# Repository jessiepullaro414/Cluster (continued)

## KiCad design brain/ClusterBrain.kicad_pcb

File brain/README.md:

# brain: the centre-screen board, the same in every car

The Toradex Verdin iMX95 carrier that runs the centre screen, with everything
that does not depend on the car or the panel: the 12 V input and surge
protection (LM74930-Q1), the 5 V buck, the 1.8 V rail, the ignition wake and
sleep control, the private CAN link to the gauges board, the audio codec and
its connectors, two USB-C host ports (J17 on USB_2 and, since 2026-11-06, J19
on USB_1; [docs/audio-and-usb.md](../docs/audio-and-usb.md)), the MFi daughterboard
header, the dial input and the bench headers.

Power (review 2026-11-03, `docs/electrical-review.md` section 9): the
ignition switches the board on through the LM74930's EN pin, and the
module's CTRL_PWR_EN_MOCI holds it on while the module is on or suspended.
So the key starts the module from any state (it boots whenever VCC
appears), and once software powers the module off with the key off, the
board draws only the LM74930's 2.5 uA shutdown current. How long to stay
suspended before powering off is a software setting.

It started as a copy of `display/` (now `archive/display-1966/`, the 1966
Mustang's one-panel carrier). The panel connector, the panel's bias supply,
its polarity jumpers and its backlight driver moved to the panel's own board
(`panel-tsd/`). In their place are two screen ports:

| Port | Ref | Video | Connector |
|---|---|---|---|
| A | J4 | MIPI DSI, 4 lanes + clock | Hirose FH12-40S, 40 contacts |
| B | J18 | LVDS0 + LVDS1 (one single- or dual-link panel) | Hirose FH12-50S, 50 contacts |

Each port has its own current-limited 5 V switch (U6, U7: TPS2557-Q1, 1.61 to
1.98 A), panel reset / enable / backlight-PWM lines held low until software
drives them, an I2C bus, and an analog panel-ID pin. The pin tables and the
rules for a panel board are in [docs/screen-ports.md](../docs/screen-ports.md),
generated from `tools/screen_ports.py`, which this board and every panel board
are built from.

The pairs from the Verdin socket to each port are planned, not autorouted
(`fan_route.py`): straight on F.Cu over the In1 GND plane, 0.16 mm, with GND
guard tracks where the socket has a ground pin between pairs and no length
difference inside a pair. The autorouter is fenced out of both corridors.

The copper that carries the 5 V rail's real current is planned as well
(`power_route.py`): L1 and the output capacitors onto a bar with four vias into
the In3 pour, J1's supply pins onto a bar with two, two at each port switch,
a wide SW_5V, and U2's PGND pins to the input capacitors and their own GND vias.
So does the battery path, J2 to both of the buck's input pins, and each screen
port's 5 V. The rest of +5V carries milliamps and stays autorouted. `route_board.py` runs
`../review/power_sheet.py` on each route, which solves the net with its pours as
copper sheets, and counts a failure as a failed attempt (2026-11-06,
[electrical review](../docs/electrical-review.md) section 9.5b).

Build: `python build_schematic.py`, `python build_pcb.py`, `python route_board.py`,
`python ../run_drc.py ClusterBrain.kicad_pcb`, `python build_bom.py`,
`python ../review/layout_checks.py brain`, `python ../review/review_netlist.py brain`,
`python ../review/usb1_topology.py`. The autorouter varies from run to run, so check
`layout_checks.py` after each route.

127.5 x 95.3 mm since the shrink of 2026-11-06 (section 9.5c of the electrical review). The empty
strips behind J4 and J18 are for the ribbons. `floorplan.py` checks every part against every other,
the corner holes and the module's keep-out.

Not known yet: whether the Verdin iMX95 drives DSI and LVDS as two independent
screens at once (the i.MX 95 itself can; question 9 in `docs/rfq-drafts.md`
section 2), and Hirose's per-contact rating and contact side for the FH12 (the
design assumes 0.5 A).

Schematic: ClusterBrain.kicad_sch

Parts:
C1: 100u 35V hybrid polymer hold-up (Panasonic EEH-ZA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; CP_Elec_8x10
C2: 1u CVS 50V; C_0805_2012Metric
C3: 100n CCAP; C_0603_1608Metric
C4: 100n CTMR; C_0603_1608Metric
C5: 4.7u CIN VIN1; C_1206_3216Metric
C6: 1u VCC; C_0603_1608Metric
C7: 100n boot; C_0603_1608Metric
C8, C54, C59: 22u COUT; C_1206_3216Metric
C9, C64: 10u CIN; C_0805_2012Metric
C10, C65: 10u COUT; C_0805_2012Metric
C11: 100n VCC; C_0603_1608Metric
C12: 100n VIO; C_0603_1608Metric
C13: 4n7 split; C_0603_1608Metric
C39: 100n; C_0603_1608Metric
C40, C44: 100n port switch IN; C_0603_1608Metric
C41, C45: 10u port switch IN; C_0805_2012Metric
C42, C46: 10u port 5V OUT; C_0805_2012Metric
C43, C47: 100n panel-ID filter; C_0603_1608Metric
C53: 10n ignition filter; C_0603_1608Metric
C55: 4.7u CIN VIN2; C_1206_3216Metric
C56: 100n CHF VIN1; C_0603_1608Metric
C57: 100n CHF VIN2; C_0603_1608Metric
C58: 22p CFF; C_0603_1608Metric
C60: 1u dial switch CIN; C_0603_1608Metric
C61: 100n dial signal filter; C_0603_1608Metric
C62: 100n dial click debounce; C_0603_1608Metric
C63: 1u dial 5V filter; C_0603_1608Metric
C66: 10u AVDD; C_0805_2012Metric
C67: 100n AVDD; C_0603_1608Metric
C68: 10u DREG; C_0805_2012Metric
C69: 100n DREG; C_0603_1608Metric
C70: 10u IOVDD; C_0805_2012Metric
C71: 100n IOVDD; C_0603_1608Metric
C72: 1u VREF; C_0603_1608Metric
C73: 1u MICBIAS; C_0603_1608Metric
C74, C75: 1u mic AC couple; C_0603_1608Metric
C76, C77, C78, C79: 4.7u line-out DC block; C_0805_2012Metric
C80, C88: 100n USB switch IN; C_0603_1608Metric
C81, C89: 10u USB switch IN; C_0805_2012Metric
C82, C90: 100u 35V hybrid polymer VBUS (Panasonic EEH-ZA1V1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; CP_Elec_8x10
C83: 1u MFi switch CIN; C_0603_1608Metric
C84: 1u MFi 5V out; C_0603_1608Metric
C85: 10n CdVdT 50V; C_0603_1608Metric
C86: 100n CIN 50V; C_0603_1608Metric
C87: 10n ignition EN filter; C_0603_1608Metric
C91: 100n USB_1_VBUS sense filter; C_0603_1608Metric
D1: SMCJ33CA bidirectional; D_SMC
D5: BAV99-Q ignition clamp (AEC-Q101); SOT-23
D6: BAV99-Q dial signal clamp (AEC-Q101); SOT-23
D7: BAV99-Q dial click clamp (AEC-Q101); SOT-23
D8, D12: SMAJ5.0A VBUS TVS; D_SMA
D9: BAV99-Q LM74930 VS supply diode (AEC-Q101); SOT-23
D10: BAV99-Q ignition EN diode (AEC-Q101); SOT-23
D11: BAV99-Q PWR_EN_MOCI hold diode (AEC-Q101); SOT-23
F1: Keystone 3568 holder, 5A Littelfuse 0297005.WXNV 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; Fuseholder_Blade_Mini_Keystone_3568
J1: Verdin iMX95 Hexa 8GB WB IT; SODIMM-260_DDR4_H4.0-5.2_OrientationStd_Socket
J2: Phoenix MKDS 1,5/3-5,08 power in (DTM06-3S pigtai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; TerminalBlock_Phoenix_MKDS-1,5-3-5.08_1x03_P5.08mm_Horizont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
J3: Molex KK-254 22-27-2031 private CAN link to gauge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; Molex_KK-254_AE-6410-03A_1x03_P2.54mm_Vertical
J4: Screen port A (MIPI DSI), Hirose FH12-40S-0.5SH; Hirose_FH12-40S-0.5SH_1x40-1MP_P0.50mm_Horizontal
J8: Samtec TSW-108-07-G-S JTAG (bench only); PinHeader_1x08_P2.54mm_Vertical
J9: Samtec TSW-104-07-G-S buttons (bench only); PinHeader_1x04_P2.54mm_Vertical
J10: RTC coin cell; BatteryHolder_Keystone_1058_1x2032
J11: Molex KK-254 22-27-2041, rotary dial (PSC-360 + c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; Molex_KK-254_AE-6410-04A_1x04_P2.54mm_Vertical
J12: Samtec TSW-103-07-G-S A55 console UART_3 1.8V (be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; PinHeader_1x03_P2.54mm_Vertical
J13: Samtec TSW-105-07-G-S USB_1 OTG (bench only); PinHeader_1x05_P2.54mm_Vertical
J14: JST XH B5B-XH-A balanced line-out L/R; JST_XH_B5B-XH-A_1x05_P2.50mm_Vertical
J15: JST XH B3B-XH-A electret microphone (2-wire + shi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; JST_XH_B3B-XH-A_1x03_P2.50mm_Vertical
J16: MFi daughterboard header I2C_1, reset, switched 5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; PinHeader_1x06_P2.54mm_Vertical; not fitted
J17, J19: GCT USB4105-GF-A USB-C 2.0 host receptacle; USB_C_Receptacle_GCT_USB4105-xx-A_16P_TopMnt_Horizontal
J18: Screen port B (LVDS), Hirose FH12-50S-0.5SH; Hirose_FH12-50S-0.5SH_1x50-1MP_P0.50mm_Horizontal
L1: 1u XEL5030-102ME 2.1MHz; L_Coilcraft_XAL5030-XXX
L2: 744230900 USB_2 common-mode choke; L_CommonMode_Wurth_WE-CNSW-0603
L3: 744230900 USB_1 common-mode choke; L_CommonMode_Wurth_WE-CNSW-0603
Q1: SQJ460AEP (AEC-Q101, 60V/20V VGS) diode; PowerPAK_SO-8L_Single
Q2: SQJ460AEP (AEC-Q101, 60V/20V VGS) pass; PowerPAK_SO-8L_Single
Q3: PMV55ENEA ignition wake pulldown; SOT-23
R1: 2m 2% sense (Susumu KRL3216E-C-R002-G-T5); R_1206_3216Metric_Kelvin
R2: 49.9R 1% RSET; R_0603_1608Metric
R3: 60.4k RILIM; R_0603_1608Metric
R4: 10k RIMON; R_0603_1608Metric
R5: 100k OV top; R_0603_1608Metric
R6: 2.05k OV bot; R_0603_1608Metric
R7: 100k UV top; R_0603_1608Metric
R8: 11.5k UV bot; R_0603_1608Metric
R9: 0R RBOOT; R_0603_1608Metric
R10: 100k FB top; R_0603_1608Metric
R11: 24.9k FB bot; R_0603_1608Metric
R12: 6.04k RT; R_0603_1608Metric
R13: 100k EN top; R_0603_1608Metric
R14: 24.9k EN bot; R_0603_1608Metric
R15: 100k FLT pu; R_0603_1608Metric
R16: 100k PG pu; R_0603_1608Metric
R17: 124k FB top; R_0603_1608Metric
R18, R60: 100k FB bot; R_0603_1608Metric
R19, R20: 60R term; R_0603_1608Metric
R21: 10k STB pd; R_0603_1608Metric
R37, R77: 61.9k 1% port ILIM (1.6-2.0 A); R_0603_1608Metric
R38, R78: 100k port 5V enable pull-down; R_0603_1608Metric
R39, R70, R79, R92: 100k FAULT pull-up to +1V8; R_0603_1608Metric
R40, R80: 10k 1% panel-ID pull-up to +1V8; R_0603_1608Metric
R41, R81: 100k panel reset pull-down; R_0603_1608Metric
R42, R82: 100k panel enable pull-down; R_0603_1608Metric
R43, R83: 100k backlight PWM pull-down; R_0603_1608Metric
R47: 10k pullup; R_0603_1608Metric
R48: 10k JTAG Vref; R_0603_1608Metric
R49: 47k min; R_0603_1608Metric
R50, R75, R84, R85: 2.2k I2C pull-up to +1V8; R_0603_1608Metric
R51: 56k ignition series; R_0603_1608Metric
R52: 33k ignition divider bottom; R_0603_1608Metric
R53: 10k wake pull-up to +1V8; R_0603_1608Metric
R54: 22.1k dial signal divider top; R_0603_1608Metric
R55: 1k dial signal series; R_0603_1608Metric
R56: 1k dial click series; R_0603_1608Metric
R57: 10k dial click pull-up to +1V8; R_0603_1608Metric
R58: 10.2k dial signal divider bottom; R_0603_1608Metric
R59: 316k 1% FB top; R_0603_1608Metric
R61: 2.2k I2C1 SDA pull-up; R_0603_1608Metric
R62: 2.2k I2C1 SCL pull-up; R_0603_1608Metric
R63: 2.2k mic bias; R_0603_1608Metric
R64: 100R mic return; R_0603_1608Metric
R65, R66, R67, R68: 100R line-out series; R_0603_1608Metric
R69: 61.9k 1% USB ILIM (1.6-2.0 A); R_0603_1608Metric
R71: 22k Rp CC1 (1.5 A, +/-5 percent or better); R_0603_1608Metric
R72: 22k Rp CC2 (1.5 A, +/-5 percent or better); R_0603_1608Metric
R73, R93: 100k USB EN pull-down; R_0603_1608Metric
R74: 100k MFi switch off in reset; R_0603_1608Metric
R76: 10k touch INT pull-up to +1V8; R_0603_1608Metric
R86: 100k SPI CS pull-up to +1V8; R_0603_1608Metric
R87: 100R RG; R_0603_1608Metric
R88: 100k ignition EN top; R_0603_1608Metric
R89: 33k ignition EN bottom; R_0603_1608Metric
R90: 100k EN pull-down; R_0603_1608Metric
R91: 100k 1% USB ILIM (0.95-1.27 A); R_0603_1608Metric
R94: 56k Rp CC1 (default USB current, +/-20 percent or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; R_0603_1608Metric
R95: 56k Rp CC2 (default USB current, +/-20 percent or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; R_0603_1608Metric
R96: 1k USB_1_VBUS sense series; R_0603_1608Metric
U1: LM74930-Q1; Texas_RGE0024H_VQFN-24-1EP_4x4mm_P0.5mm_EP2.7x2.7mm
U2: LM61460-Q1; TI_RJR0014A_VQFN-HR-14_4x3.5mm
U3: TLV767-Q1; Texas_DRB0008A
U4: TCAN1044V-Q1; SOIC-8_3.9x4.9mm_P1.27mm
U6, U7, U11, U16: TPS2557-Q1; Texas_DRB0008A
U8: TPS22918-Q1 (AEC-Q100 G2) dial 5V switch; SOT-23-6
U9: TAC5112-Q1; QFN-32-1EP_5x5mm_P0.5mm_EP3.7x3.7mm_ThermalVias
U10: TLV767-Q1 (3.3 V audio AVDD); Texas_DRB0008A
U12: TPD4E02B04-Q1 line-out ESD (bidirectional, review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; USON-10_2.5x1.0mm_P0.5mm
U13: TPD4E05U06-Q1 mic ESD; USON-10_2.5x1.0mm_P0.5mm
U14, U17: TPD4E05U06-Q1 USB ESD; USON-10_2.5x1.0mm_P0.5mm
U15: TPS22918-Q1 (AEC-Q100 G2) MFi 5V switch; SOT-23-6

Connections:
+1V8: C10.1, C12.1, C70.1, C71.1, D6.2 (K2), D7.2 (K2), J4.7 (+1V8), J16.6 (V1V8), J18.42 (+1V8), R17.1, R39.2, R40.2, R47.2, R48.2, R50.2, R53.1, R57.1, R61.2, R62.2, R70.2, R75.2, R76.2, R79.2, R80.2, R84.2, R85.2, R86.2, R92.2, U3.1 (OUT), U4.5 (VIO), U9.7 (IOVDD)
+3V3: C65.1, C66.1, C67.1, R59.1, U9.31 (AVDD), U10.1 (OUT)
+5V: C8.1, C9.1, C11.1, C40.1, C41.1, C44.1, C45.1, C54.1, C58.1, C59.1, C60.1, C64.1, C80.1, C81.1, C83.1, C88.1, C89.1, D5.2 (K2), J1.251 (VCC), J1.253 (VCC), J1.255 (VCC), J1.257 (VCC), J1.259 (VCC), L1.2, R10.1, R15.2, R16.2, R71.2, R72.2, R94.2, R95.2, U2.1 (BIAS), U3.8 (IN), U4.3 (VCC), U6.2 (IN1), U6.3 (IN2), U7.2 (IN1), U7.3 (IN2), U8.1 (VIN), U10.8 (IN), U11.2 (IN1), U11.3 (IN2), U15.1 (VIN), U16.2 (IN1), U16.3 (IN2)
+12V_PROT: C1.1, C5.1, C55.1, C56.1, C57.1, R1.2, R13.1, U2.8 (VIN1), U2.12 (VIN2)
AOUT_L_N: R66.1, U9.27 (OUT1M)
AOUT_L_N_R: C77.1, R66.2
AOUT_L_P: R65.1, U9.28 (OUT1P)
AOUT_L_P_R: C76.1, R65.2
AOUT_R_N: R68.1, U9.30 (OUT2M)
AOUT_R_N_R: C79.1, R68.2
AOUT_R_P: R67.1, U9.29 (OUT2P)
AOUT_R_P_R: C78.1, R67.2
BOOT_C: C7.1, R9.2, U2.14 (CBOOT)
BOOT_R: R9.1, U2.13 (RBOOT)
BRAIN_EN: D10.3 (CA), D11.3 (CA), R90.1, U1.6 (EN)
CAN1_H: J3.1 (CANH), R19.1, U4.7 (CANH)
CAN1_L: J3.2 (CANL), R20.2, U4.6 (CANL)
CAN1_RXD: J1.22 (CAN_1_RX), U4.4 (RXD)
CAN1_SPLIT: C13.1, R19.2, R20.1
CAN1_STB: R21.1, U4.8 (STB)
CAN1_TXD: J1.20 (CAN_1_TX), U4.1 (TXD)
CAP_CP: C3.1, U1.23 (CAP)
CODEC_DREG: C68.1, C69.1, U9.2 (DREG)
CODEC_MICBIAS: C73.1, R63.1, U9.17 (MICBIAS)
CODEC_VREF: C72.1, U9.32 (VREF)
COMMON: Q1.1 (S1), Q1.2 (S2), Q1.3 (S3), Q2.1 (S1), Q2.2 (S2), Q2.3 (S3), U1.2 (A), U1.15 (OUT)
CS_MINUS: R1.4 (S2), U1.19 (CS-)
CS_PLUS: R2.2, U1.20 (CS+)
DGATE: Q1.4 (G), U1.1 (DGATE)
DIAL_5V: C63.1, J11.1 (DIAL_5V), U8.6 (VOUT)
DIAL_ADC: C61.1, D6.3 (CA), J1.2 (ADC_1), R55.2
DIAL_CLICK: C62.1, D7.3 (CA), J1.206 (GPIO_1), R56.2, R57.2
DIAL_CLICK_RAW: J11.4 (CLICK), R56.1
DIAL_DIV: R54.2, R55.1, R58.1
DIAL_SIG_RAW: J11.2 (SIG), R54.1
DSI_CLK_N: J1.35 (DSI_1_CLK_N), J4.15 (DSI_CLK_N)
DSI_CLK_P: J1.37 (DSI_1_CLK_P), J4.16 (DSI_CLK_P)
DSI_D0_N: J1.47 (DSI_1_D0_N), J4.21 (DSI_D0_N)
DSI_D0_P: J1.49 (DSI_1_D0_P), J4.22 (DSI_D0_P)
DSI_D1_N: J1.41 (DSI_1_D1_N), J4.18 (DSI_D1_N)
DSI_D1_P: J1.43 (DSI_1_D1_P), J4.19 (DSI_D1_P)
DSI_D2_N: J1.29 (DSI_1_D2_N), J4.12 (DSI_D2_N)
DSI_D2_P: J1.31 (DSI_1_D2_P), J4.13 (DSI_D2_P)
DSI_D3_N: J1.23 (DSI_1_D3_N), J4.9 (DSI_D3_N)
DSI_D3_P: J1.25 (DSI_1_D3_P), J4.10 (DSI_D3_P)
EN_5V: R13.2, R14.1, U2.7 (EN/SYNC)
FB_1V8: R17.2, R18.1, U3.3 (FB)
FB_3V3: R59.2, R60.1, U10.3 (FB)
FB_5V: C58.2, R10.2, R11.1, U2.4 (FB)
GND: C1.2, C2.2, C4.2, C5.2, C6.2, C8.2, C9.2, C10.2, C11.2, C12.2, C13.2, C39.2, C40.2, C41.2, C42.2, C43.2, C44.2, C45.2, C46.2, C47.2, C53.2, C54.2, C55.2, C56.2, C57.2, C59.2, C60.2, C61.2, C62.2, C63.2, C64.2, C65.2, C66.2, C67.2, C68.2, C69.2, C70.2, C71.2, C72.2, C73.2, C80.2, C81.2, C82.2, C83.2, C84.2, C85.2, C86.2, C87.2, C88.2, C89.2, C90.2, C91.2, D1.2, D5.1 (A1), D6.1 (A1), D7.1 (A1), D8.2, D12.2, J1.10 (GND), J1.11 (GND), J1.18 (GND), J1.27 (GND), J1.28 (GND), J1.33 (GND), J1.39 (GND), J1.40 (GND), J1.45 (GND), J1.50 (GND), J1.51 (GND), J1.65 (GND), J1.68 (GND), J1.71 (GND), J1.77 (GND), J1.83 (GND), J1.86 (GND), J1.89 (GND), J1.97 (GND), J1.98 (GND), J1.103 (GND), J1.109 (GND), J1.110 (GND), J1.115 (GND), J1.121 (GND), J1.122 (GND), J1.127 (GND), J1.134 (GND), J1.145 (GND), J1.146 (GND), J1.158 (GND), J1.167 (GND), J1.170 (GND), J1.173 (GND), J1.179 (GND), J1.182 (GND), J1.194 (GND), J1.195 (GND), J1.204 (GND), J1.209 (GND), J1.223 (GND), J1.224 (GND), J1.229 (GND), J1.230 (GND), J1.236 (GND), J1.242 (GND), J1.243 (GND), J2.2 (GND), J3.3 (GND), J4.1 (GND), J4.6 (GND), J4.8 (GND), J4.11 (GND), J4.14 (GND), J4.17 (GND), J4.20 (GND), J4.23 (GND), J4.28 (GND), J4.33 (GND), J4.38 (GND), J4.39 (GND), J4.40 (GND), J8.8 (GND), J9.4 (GND), J10.2 (GND), J11.3 (GND), J12.3 (GND), J13.5 (GND), J14.5 (GND), J15.3 (GND), J16.4 (GND), J17.A1 (A1_GND), J17.A12 (A12_GND), J17.B1 (B1_GND), J17.B12 (B12_GND), J17.SH (SHIELD), J18.1 (GND), J18.11 (GND), J18.14 (GND), J18.17 (GND), J18.20 (GND), J18.23 (GND), J18.26 (GND), J18.29 (GND), J18.32 (GND), J18.35 (GND), J18.38 (GND), J18.41 (GND), J18.43 (GND), J18.44 (GND), J18.50 (GND), J19.A1 (A1_GND), J19.A12 (A12_GND), J19.B1 (B1_GND), J19.B12 (B12_GND), J19.SH (SHIELD), Q3.2 (S), R3.2, R4.2, R6.2, R8.2, R11.2, R12.2, R14.2, R18.2, R21.2, R37.2, R38.2, R41.2, R42.2, R43.2, R52.2, R58.2, R60.2, R64.2, R69.2, R73.2, R74.2, R77.2, R78.2, R81.2, R82.2, R83.2, R89.2, R90.2, R91.2, R93.2, U1.13 (GND), U2.3 (AGND), U2.9 (PGND1), U2.11 (PGND2), U3.4 (GND), U3.6 (GND2), U3.9 (EP), U4.2 (GND), U6.1 (GND), U6.9 (EP), U7.1 (GND), U7.9 (EP), U8.2 (GND), U9.1 (VSS1), U9.8 (VSS2), U9.15 (VSS3), U9.16 (ADDR), U9.22 (VSSI1), U9.23 (VSSI2), U9.24 (VSSI3), U9.25 (VSSI4), U9.26 (VSS4), U9.33 (EP), U10.4 (GND), U10.6 (GND2), U10.9 (EP), U11.1 (GND), U11.9 (EP), U12.3 (GND1), U12.8 (GND2), U13.3 (GND1), U13.8 (GND2), U14.3 (GND1), U14.8 (GND2), U15.2 (GND), U16.1 (GND), U16.9 (EP), U17.3 (GND1), U17.8 (GND2); also elsewhere on the board
HGATE: Q2.4 (G), R87.1, U1.14 (HGATE)
HGATE_DVDT: C85.1, R87.2
I2C1_SCL: J1.14 (I2C_1_SCL), J16.2 (SCL), R62.1, U9.9 (SCL)
I2C1_SDA: J1.12 (I2C_1_SDA), J16.1 (SDA), R61.1, U9.10 (SDA)
I2S_BCLK: J1.30 (I2S_1_BCLK), U9.3 (BCLK)
I2S_DIN: J1.34 (I2S_1_D_OUT), U9.6 (DIN)
I2S_DOUT: J1.36 (I2S_1_D_IN), U9.5 (DOUT)
I2S_FSYNC: J1.32 (I2S_1_SYNC), U9.4 (FSYNC)
IGN_EN_DIV: C87.1, D10.1 (A1), R88.2, R89.1
IGN_GATE: C53.1, D5.3 (CA), Q3.1 (G), R51.2, R52.1
IGN_SENSE: J2.3 (IGN), R51.1, R88.1
IGN_WAKE_N: J1.252 (CTRL_WAKE1_MICO#), Q3.3 (D), R53.2
ILIM: R3.1, U1.11 (ILIM)
IMON: R4.1, U1.10 (IMON)
JTAG_TCK: J1.9 (JTAG_1_TCK), J8.3 (TCK)
JTAG_TDI: J1.1 (JTAG_1_TDI), J8.5 (TDI)
JTAG_TDO: J1.5 (JTAG_1_TDO), J8.4 (TDO)
JTAG_TMS: J1.13 (JTAG_1_TMS), J8.2 (TMS)
JTAG_TRST: J1.3 (JTAG_1_TRST#), J8.6 (TRST)
JTAG_VREF: J1.7 (JTAG_1_VREF), J8.1 (VREF), R48.1
LINE_L_N: C77.2, J14.2 (L_N), U12.2 (CH2)
LINE_L_P: C76.2, J14.1 (L_P), U12.1 (CH1)
LINE_R_N: C79.2, J14.4 (R_N), U12.5 (CH4)
LINE_R_P: C78.2, J14.3 (R_P), U12.4 (CH3)
LM_VS: C2.1, C3.2, D9.3 (CA), U1.7 (MODE), U1.22 (VS)
LVDS0_CLK_N: J1.88 (LVDS0_CLK_N), J18.40 (LVDS0_CLK_N)
LVDS0_CLK_P: J1.90 (LVDS0_CLK_P), J18.39 (LVDS0_CLK_P)
LVDS0_D0_N: J1.94 (LVDS0_D0_N), J18.37 (LVDS0_D0_N)
LVDS0_D0_P: J1.96 (LVDS0_D0_P), J18.36 (LVDS0_D0_P)
LVDS0_D1_N: J1.100 (LVDS0_D1_N), J18.34 (LVDS0_D1_N)
LVDS0_D1_P: J1.102 (LVDS0_D1_P), J18.33 (LVDS0_D1_P)
LVDS0_D2_N: J1.106 (LVDS0_D2_N), J18.31 (LVDS0_D2_N)
LVDS0_D2_P: J1.108 (LVDS0_D2_P), J18.30 (LVDS0_D2_P)
LVDS0_D3_N: J1.112 (LVDS0_D3_N), J18.28 (LVDS0_D3_N)
LVDS0_D3_P: J1.114 (LVDS0_D3_P), J18.27 (LVDS0_D3_P)
LVDS1_CLK_N: J1.118 (LVDS1_CLK_N), J18.25 (LVDS1_CLK_N)
LVDS1_CLK_P: J1.120 (LVDS1_CLK_P), J18.24 (LVDS1_CLK_P)
LVDS1_D0_N: J1.124 (LVDS1_D0_N), J18.22 (LVDS1_D0_N)
LVDS1_D0_P: J1.126 (LVDS1_D0_P), J18.21 (LVDS1_D0_P)
LVDS1_D1_N: J1.130 (LVDS1_D1_N), J18.19 (LVDS1_D1_N)
LVDS1_D1_P: J1.132 (LVDS1_D1_P), J18.18 (LVDS1_D1_P)
LVDS1_D2_N: J1.136 (LVDS1_D2_N), J18.16 (LVDS1_D2_N)
LVDS1_D2_P: J1.138 (LVDS1_D2_P), J18.15 (LVDS1_D2_P)
LVDS1_D3_N: J1.142 (LVDS1_D3_N), J18.13 (LVDS1_D3_N)
LVDS1_D3_P: J1.144 (LVDS1_D3_P), J18.12 (LVDS1_D3_P)
MFI_5V: C84.1, J16.5 (VSW), U15.6 (VOUT)
MFI_PWR_EN: J1.210 (GPIO_3), R74.1, U15.3 (ON)
MFI_RST_N: J1.208 (GPIO_2), J16.3 (RST_N)
MIC_IN_N: C75.2, U9.19 (IN1M)
MIC_IN_P: C74.2, U9.18 (IN1P)
MIC_N: C75.1, J15.2 (MIC_N), R64.1, U13.2 (CH2)
MIC_P: C74.1, J15.1 (MIC_P), R63.2, U13.1 (CH1)
OV_DIV: R5.2, R6.1, U1.5 (OV), U1.16 (OVCLAMP)
PG_5V: R16.1, U2.5 (PGOOD)
PORTA_5V: C42.1, J4.2 (PORTA_5V), J4.3 (PORTA_5V), J4.4 (PORTA_5V), J4.5 (PORTA_5V), U6.6 (OUT1), U6.7 (OUT2)
PORTA_BL_PWM: J1.19 (PWM_3_DSI), J4.26 (PORTA_BL_PWM), R43.1
PORTA_EN: J1.21 (GPIO_10_DSI), J4.25 (PORTA_EN), R42.1
PORTA_FLT_N: J1.220 (GPIO_7_CSI), R39.1, U6.8 (FAULT)
PORTA_ID: C43.1, J1.4 (ADC_2), J4.32 (PORTA_ID), R40.1
PORTA_ILIM: R37.1, U6.5 (ILIM)
PORTA_INT: J1.148 (GPIO_IO34), J4.31 (PORTA_INT), R76.1
PORTA_PWR_EN: J1.152 (GPIO_IO04), R38.1, U6.4 (EN)
PORTA_RESET: J1.17 (GPIO_9_DSI), J4.24 (PORTA_RESET), R41.1
PORTA_SCL: J1.55 (I2C_2_DSI_SCL), J4.30 (PORTA_SCL), R75.1
PORTA_SDA: J1.53 (I2C_2_DSI_SDA), J4.29 (PORTA_SDA), R50.1
PORTA_TE: J1.150 (GPIO_IO33), J4.27 (PORTA_TE)
PORTB_5V: C46.1, J18.45 (PORTB_5V), J18.46 (PORTB_5V), J18.47 (PORTB_5V), J18.48 (PORTB_5V), J18.49 (PORTB_5V), U7.6 (OUT1), U7.7 (OUT2)
PORTB_BL_PWM: J1.15 (PWM_1), J18.8 (PORTB_BL_PWM), R83.1
PORTB_EN: J1.216 (GPIO_5_CSI), J18.9 (PORTB_EN), R82.1
PORTB_FLT_N: J1.222 (GPIO_8_CSI), R79.1, U7.8 (FAULT)
PORTB_ID: C47.1, J1.6 (ADC_3), J18.2 (PORTB_ID), R80.1
PORTB_ILIM: R77.1, U7.5 (ILIM)
PORTB_PWR_EN: J1.154 (GPIO_IO07), R78.1, U7.4 (EN)
PORTB_RESET: J1.212 (GPIO_4), J18.10 (PORTB_RESET), R81.1
PORTB_SCL: J1.59 (I2C_3_HDMI_SCL), J18.6 (PORTB_SCL), R85.1
PORTB_SDA: J1.57 (I2C_3_HDMI_SDA), J18.7 (PORTB_SDA), R84.1
PORTB_SPI_CLK: J1.196 (SPI_1_CLK), J18.5 (PORTB_SPI_CLK)
PORTB_SPI_CS: J1.202 (SPI_1_CS), J18.3 (PORTB_SPI_CS), R86.1
PORTB_SPI_MOSI: J1.200 (SPI_1_MOSI), J18.4 (PORTB_SPI_MOSI)
PWR_BTN: J1.248 (CTRL_PWR_BTN_MICO#), J9.1 (PWR_BTN)
PWR_EN_MOCI: D11.1 (A1), J1.254 (CTRL_PWR_EN_MOCI), U3.5 (EN), U10.5 (EN)
PWR_FLT: R15.1, U1.12 (FLT)
RECOVERY: J1.246 (CTRL_RECOVERY_MICO#), J9.2 (RECOVERY)
RESET_MICO: J1.260 (CTRL_RESET_MICO#), J8.7 (RESET), J9.3 (RESET)
RESET_MOCI: J1.258 (CTRL_RESET_MOCI#), R47.1
RT_5V: R12.1, U2.6 (RT)
SENSE_HI: Q1.5 (D), R1.1, U1.24 (C)
SENSE_TAP: R1.3 (S1), R2.1, U1.18 (ISCP)
SLEEP_MOCI: J1.256 (CTRL_SLEEP_MOCI#), U8.3 (ON)
SW_5V: C7.2, L1.1, U2.10 (SW)
SW_SENSE: R5.1, R7.1, U1.3 (SW)
TMR: C4.1, U1.9 (TMR)
UART_RXD: J1.147 (UART_3_RXD), J12.2 (RXD)
UART_TXD: J1.149 (UART_3_TXD), J12.1 (TXD)
USB1_CC1: J19.A5 (A5_CC1), R94.1, U17.4 (CH3), U17.7 (CH3_THRU)
USB1_CC2: J19.B5 (B5_CC2), R95.1, U17.5 (CH4), U17.6 (CH4_THRU)
USB1_C_DN: J19.A7 (A7_DN), J19.B7 (B7_DN), L3.4 (C_N), U17.2 (CH2), U17.9 (CH2_THRU)
USB1_C_DP: J19.A6 (A6_DP), J19.B6 (B6_DP), L3.1 (C_P), U17.1 (CH1), U17.10 (CH1_THRU)
USB1_EN: J1.155 (USB_1_EN), R93.1, U16.4 (EN)
USB1_ILIM: R91.1, U16.5 (ILIM)
USB1_OC_N: J1.157 (USB_1_OC#), R92.1, U16.8 (FAULT)
USB1_VBUS: C90.1, D12.1, J19.A9 (A9_VBUS), J19.B4 (B4_VBUS), R96.1, U16.6 (OUT1), U16.7 (OUT2)
USB1_VBUS_L: J19.A4 (A4_VBUS), J19.B9 (B9_VBUS)
USB2_CC1: J17.A5 (A5_CC1), R71.1, U14.4 (CH3)
USB2_CC2: J17.B5 (B5_CC2), R72.1, U14.5 (CH4)
USB2_C_DN: J17.A7 (A7_DN), J17.B7 (B7_DN), L2.4 (C_N), U14.2 (CH2)
USB2_C_DP: J17.A6 (A6_DP), J17.B6 (B6_DP), L2.1 (C_P), U14.1 (CH1)
USB2_DN: J1.181 (USB_2_D_N), L2.3 (M_N)
USB2_DP: J1.183 (USB_2_D_P), L2.2 (M_P)
USB2_EN: J1.185 (USB_2_EN), R73.1, U11.4 (EN)
USB2_ILIM: R69.1, U11.5 (ILIM)
USB2_OC_N: J1.187 (USB_2_OC#), R70.1, U11.8 (FAULT)
USB2_VBUS: C82.1, D8.1, J17.A9 (A9_VBUS), J17.B4 (B4_VBUS), U11.6 (OUT1), U11.7 (OUT2)
USB2_VBUS_L: J17.A4 (A4_VBUS), J17.B9 (B9_VBUS)
USB_DN: J1.163 (USB_1_D_N), J13.2 (D_N), L3.3 (M_N)
USB_DP: J1.165 (USB_1_D_P), J13.3 (D_P), L3.2 (M_P)
USB_ID: J1.161 (USB_1_ID), J13.4 (ID)
USB_VBUS: C91.1, J1.159 (USB_1_VBUS), J13.1 (VBUS), R96.2
UVLO_DIV: R7.2, R8.1, U1.4 (UVLO)
VBACKUP: C39.1, J1.249 (VCC_BACKUP), R49.2
VBACKUP_CELL: J10.1 (VBAT), R49.1
VBAT_F: C86.1, D1.1, D9.1 (A1), F1.2, Q2.5 (D)
VBAT_IN: F1.1, J2.1 (VBAT)
VCC_LDO: C6.1, U2.2 (VCC)

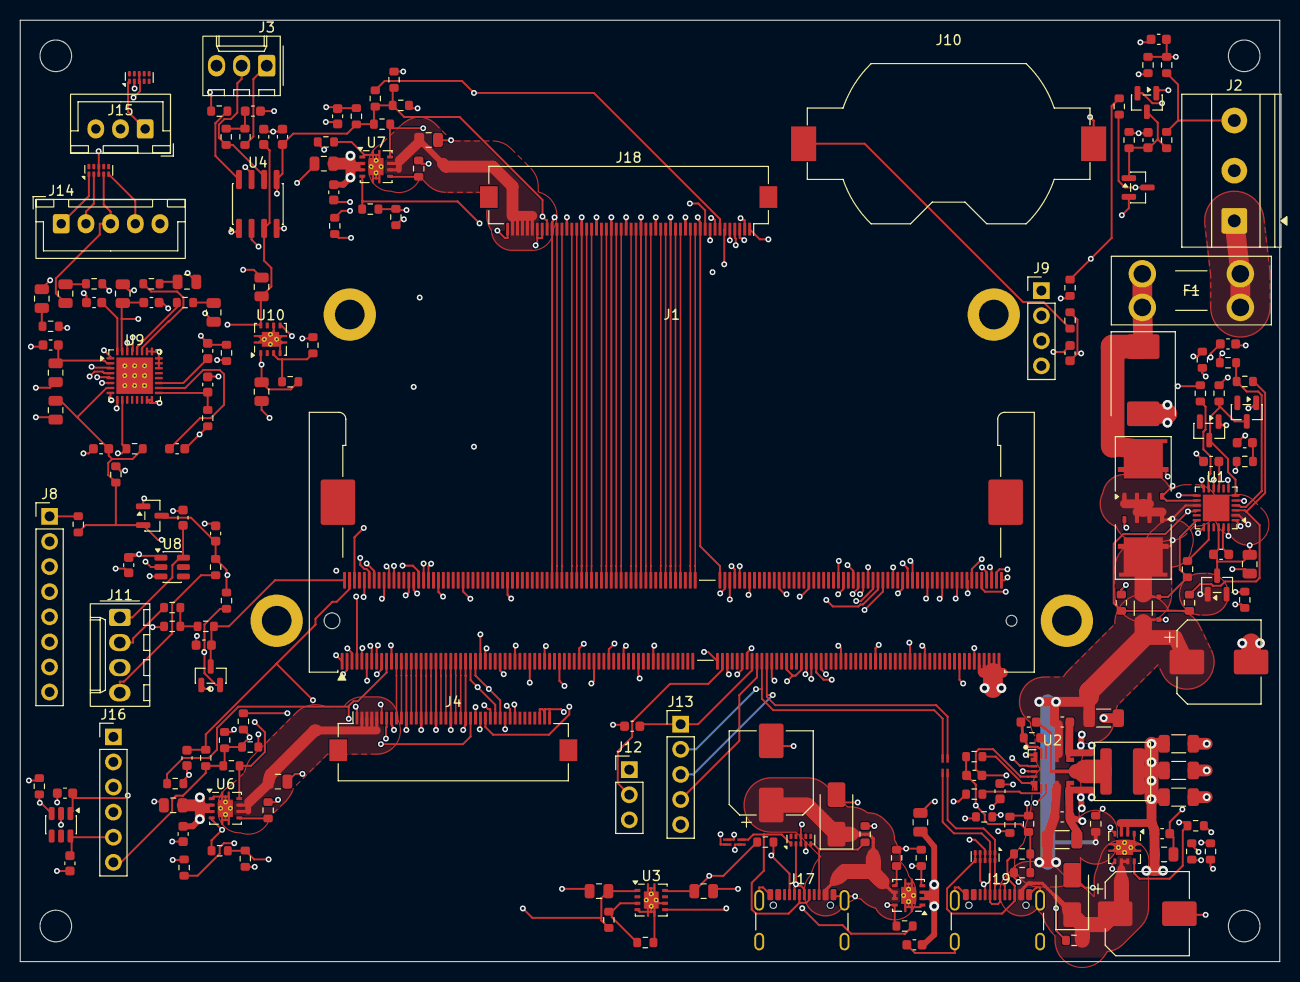
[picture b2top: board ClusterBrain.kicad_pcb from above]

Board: 6 copper layers, 127.5 x 95.3 mm, 195 parts (0 on the bottom side), 174 nets.

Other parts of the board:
MH1, MH2, MH3, MH4: MountingHole_3.2mm_M3
S1, S2: M2x0.4 SMD standoff 2.5 mm; MountingHole_2.2mm_M2_Pad
S3, S4: M2x0.4 SMD standoff 7.0 mm; MountingHole_2.2mm_M2_Pad

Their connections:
GND: S1.1, S2.1, S3.1, S4.1; also elsewhere on the board

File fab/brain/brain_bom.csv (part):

Manufacturer Part Number,Manufacturer,Quantity,Designators,Package,Category,Description,Status
BAV99-Q (confirm reel suffix at order time),Nexperia,3,D5-D7,SOT-23,Semiconductors,"Dual series high-speed switching diode, SOT-23, clamps the ignition-wake gate node to GND and +5V (pin 3 signal, pin 1 GND, pin 2 +5V; datasheet Rev. 8)",ok
TPS2557QDRBRQ1,TI,3,"U6, U7, U11",Texas_DRB0008A,Semiconductors,"Automotive adjustable current-limited power switch, active-HIGH enable, USB host VBUS, S-PVSON-8 DRB (datasheet SLVSC97B, Active Production; the active-low sibling is TPS2556-Q1, do NOT substitute)",ok
SQJ460AEP-T1_GE3 (confirm the reel suffix on Vishay doc 79771 at order time),Vishay,2,"Q1, Q2",PowerPAK_SO-8L_Single,Semiconductors,"60V N-ch MOSFET, VGS +-20V, 8.7mR max at 10V, IDM 180A, PowerPAK SO-8L - back-to-back ideal-diode/pass FET pair for the LM74930-Q1 (replaces PMV55ENEA: NRND, 12.6A pulse rating vs ~27A in ISO 7637-2 pulse 2a, 262 C/W; review X-01, X-02, D-05)",ok
TLV76701QWDRBRQ1,TI,2,"U3, U10",Texas_DRB0008A,Semiconductors,"Automotive 16V/1A adjustable LDO, two on this board: U3 = +1V8 Verdin I/O rail, U10 = +3V3 audio codec AVDD (divider 316k/100k), VSON-8 DRB with wettable flanks (datasheet SBVS381A); 01 = adjustable, QW = wettable-flank automotive",ok
TPD4E05U06QDQARQ1,TI,2,"U13, U14",USON-10_2.5x1.0mm_P0.5mm,Semiconductors,"Automotive 4-channel ESD array, 0.5 pF, 5.5 V, IEC 61000-4-2 +/-12 kV, USON-10 DQA 2.5x1.0 mm (datasheet SLVSCO7C, Active Production). Used on the USB D+/D-/CC lines, the four line-out legs and the microphone pair",ok
TPS22918TDBVRQ1,TI,2,"U8, U15",SOT-23-6,Semiconductors,"Automotive 1-5.5V 2A load switch, SOT-23-6, switches the rotary dial sensor's 5V off in sleep (ON driven by the Verdin's CTRL_SLEEP_MOCI#; datasheet SLVSCZ8B); TI lists it Active",ok
LM61460AASQRJRRQ1,TI,1,U2,TI_RJR0014A_VQFN-HR-14_4x3.5mm,Semiconductors,"Automotive 3-36V 6A low-EMI synchronous buck, main +5V rail, VQFN-HR-14 RJR (datasheet SNVSB70F). LM61460 is a FAMILY of three adjustable variants: AAS (auto light-load mode + spread spectrum, chosen), AAN (auto, no spread spectrum), AFS (forced-PWM + spread spectrum). AAS was picked for EMI; use AFS if PFM ripple at light load is a problem. Not yet bench-verified",ok
LM74930QRGERQ1,TI,1,U1,Texas_RGE0024H_VQFN-24-1EP_4x4mm_P0.5mm_EP2.7x2.7mm,Semiconductors,"Automotive ideal-diode surge stopper w/ circuit breaker + OV clamp, VQFN-24 RGE (datasheet SNOSDF6); TI lists it Active/Production",ok
PMV55ENEAR,Nexperia,1,Q3,SOT-23,Semiconductors,"60V N-ch MOSFET, VGS +-20V, 3.1A, SOT-23 - back-to-back ideal-diode/pass FET pair (orderable suffix R = reel; 12NC 934068714215)",ok
SMAJ5.0A (multi-source; PATTERN - choose an AEC-Q101 listed variant at order time),Littelfuse / Vishay / Bourns,1,D8,D_SMA,Semiconductors,"400 W SMA 5 V TVS, 6.4 V min breakdown, on USB VBUS: a hot-plugged cable can ring above the TPS2557-Q1's 7 V absolute maximum. The AEC-Q101 qualification of a specific vendor's SMAJ5.0A was not checked",ok
SMCJ33A (multi-source),Littelfuse / onsemi / Vishay (industry-standard P/N),1,D1,D_SMC,Semiconductors,"SMC-package TVS diode, 33V standoff, 12V-rail transient protection - not pinned to one vendor, real industry-standard part number, same real part gauges/'s own D1 already uses",ok
TAC5112WQRTVRQ1,TI,1,U9,QFN-32-1EP_5x5mm_P0.5mm_EP3.7x3.7mm_ThermalVias,Semiconductors,"Automotive low-power stereo audio codec (2-ch ADC, 2-ch DAC), 1.8 V I/O, AVDD 1.8/3.3 V, I2S/TDM, I2C, WQFN-32 RTV 5x5 mm (datasheet SLASFC2A, Active Production, 3000-piece reel; the Q1 datasheet is a separate document from the TAC5112 non-automotive one)",ok
TCAN1044VDRQ1,TI,1,U4,SOIC-8_3.9x4.9mm_P1.27mm,Semiconductors,"Automotive CAN FD transceiver w/ 1.8V I/O support (V variant is load-bearing - see parts.py), SOIC-8 D (datasheet SLLSF17D)",ok
TPD4E02B04QDQARQ1,TI,1,U12,USON-10_2.5x1.0mm_P0.5mm,Semiconductors,"Automotive 4-channel BIDIRECTIONAL ESD array, VRWM +-3.6 V, 0.25 pF, IEC 61000-4-2 +/-12 kV, USON-10 DQA 2.5x1.0 mm (datasheet SLVSDZ2A, Active Production). On the four line-out legs, which swing below ground on the connector side of the DC-blocking capacitors (review D-11)",ok
XEL5030-102MEC,Coilcraft,1,L1,L_Coilcraft_XAL5030-XXX,Semiconductors,"1uH shielded molded power inductor for the LM61460-Q1 5V buck at 2.1MHz: Isat 16.9A vs the 11.5A max high-side current limit, DCR 7mR typ, 5.5x5.3x3.1mm, AEC-Q200; the part the LM61460-Q1 datasheet's Table 10-5 used for 5V/2.1MHz (Coilcraft Document 1412-2; trailing C = 7in reel ordering code)",ok
0297005.WXNV,Littelfuse,1,F1 (fuse element),Mini blade (element),Electromechanical,"5A MINI blade fuse element, 32V, 1kA interrupt rating at 32V, -40..+125C (one per board; plugs into the F1 holder)",ok
3568,Keystone Electronics,1,F1,Fuseholder_Blade_Mini_Keystone_3568,Electromechanical,"Mini blade fuse holder, PCB mount - same real holder gauges/ uses. REVIEW FIX 2026-10-03: replaces the Bourns MF-RG500 PTC (16V max, -40..+85C, not rated for jump start or load dump). The 5A fuse element is the next line",ok
1058,Keystone Electronics,1,J10,BatteryHolder_Keystone_1058_1x2032,Connectors,"20mm coin cell (2032) holder, real unambiguous Keystone part number - same real numbering convention as this family's own Keystone 3568 fuse holder, identified from the real footprint name rather than an independent datasheet citation in build_schematic.py's own comments",ok
22-27-2031,Molex,1,J3,Molex_KK-254_AE-6410-03A_1x03_P2.54mm_Vertical,Connectors,"3-circuit KK 254 (2.54mm) vertical header, board side of the private CAN link to gauges/ J8 (CANH / CANL / GND), 4A / 250V per contact. The display is not on the car bus. Mating (docs/harness.md): Molex KK 254 housing 22-01-3037 with 08-50-0114 crimps (22-30 AWG) at both ends, a short in-dash twisted-pair cable, no DTM connector",ok
22-27-2041,Molex,1,J11,Molex_KK-254_AE-6410-04A_1x04_P2.54mm_Vertical,Connectors,"4-circuit KK 254 (2.54mm) vertical header for the rotary dial: sensor 5V (switched), sensor signal, ground, click switch. Same KK 254 family as J3 (22-27-2031); mating housing and crimps are separate Molex KK 254 parts",ok
2309409-2,TE Connectivity,1,J1,SODIMM-260_DDR4_H4.0-5.2_OrientationStd_Socket,Connectors,"260-position DDR4 SODIMM socket, 5.2mm stack - the socket Toradex recommends in datasheet section 6.5.1 (docs.toradex.com/200007-verdin_imx95_datasheet.pdf), matching this board's SODIMM-260_DDR4_H4.0-5.2 footprint. The Verdin SoM that plugs into it is its own line under Companion parts (review 2026-10-03: the two were one line)",ok
B3B-XH-A(LF)(SN),JST,1,J15,JST_XH_B3B-XH-A_1x03_P2.50mm_Vertical,Connectors,"3-circuit XH 2.50 mm vertical header, 2-wire electret microphone: bias+signal, return, shield. Mating: XHP-3 housing with SXH-001T-P0.6 crimps. PATTERN: confirm the ordering suffix in the cart",ok
B5B-XH-A(LF)(SN),JST,1,J14,JST_XH_B5B-XH-A_1x05_P2.50mm_Vertical,Connectors,"5-circuit XH 2.50 mm vertical header, balanced stereo line-out: L+, L-, R+, R-, GND. Mating: XHP-5 housing with SXH-001T-P0.6 crimps. PATTERN: ordering suffix (LF)(SN) is JST's lead-free tin variant, confirm in the cart. Deliberately a different family from the KK 254 headers so audio cannot be mated to the CAN or dial headers",ok
FH12-40S-0.5SH(55),Hirose,1,J4,Hirose_FH12-40S-0.5SH_1x40-1MP_P0.50mm_Horizontal,Connectors,"Screen port A (MIPI DSI): 40-position 0.5 mm-pitch FFC connector, back-flip lock, 1.0 mm high (KiCad Hirose_FH12-40S-0.5SH footprint). Pin order in tools/screen_ports.py and docs/screen-ports.md. PATTERN: (55) is the tape-and-reel suffix, confirm in the cart, and confirm the 0.5 A per-contact rating against the current datasheet",ok
FH12-50S-0.5SH(55),Hirose,1,J18,Hirose_FH12-50S-0.5SH_1x50-1MP_P0.50mm_Horizontal,Connectors,"Screen port B (LVDS0 + LVDS1): 50-position 0.5 mm-pitch FFC connector, same family as J4 (different count so the two cables cannot be swapped). PATTERN: confirm the (55) suffix in the cart",ok
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
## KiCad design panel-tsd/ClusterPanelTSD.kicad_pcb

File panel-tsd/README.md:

# panel-tsd: panel board for the TSD TST040HDBC-42

A small board that sits behind the Team Source Display TST040HDBC-42 (4.0 in
round, 720 x 720, 800 nits, native MIPI DSI) and carries everything that belongs
to that panel:

* J4, the panel's 39-pin FPC connector (Hirose FH26-39S, inferred: the panel
  datasheet does not name one);
* U6, the TPS65131-Q1 bias supply, set to +5.98 V / -6.05 V (inside the ICNL9707
  driver's 4.5 to 6.5 V range), with the open polarity jumpers JP1/JP2 because the
  panel datasheet's table and drawing disagree on which pins take which rail;
* U7, the TPS61165-Q1 backlight boost, 182 mA into the panel's 15 V LED string;
* J1, the input from the brain board's screen port A (Hirose FH12-40S, same pin
  order, [docs/screen-ports.md](../docs/screen-ports.md)), and R1, the 2.0 k
  panel-ID resistor.

The circuits are display/'s, moved here unchanged (same designators). Before
bridging JP1/JP2, check the real panel with a meter's diode test
(`fab/README.md`).

The DSI pairs (three lanes and the clock) are autorouted on F.Cu and B.Cu only,
the two layers right above a solid GND plane, at 0.16 mm: each leg is about 52
ohm on its own, so a pair stays near 100 ohm even where the router separates its
legs. They have to cross on the way (the port carries each pair N then P in the
Verdin's lane order, the panel FPC P then N in its own), so the router uses a few
vias. `route_board.py` prints each leg's length and the skew inside each pair.

Six layers (JLC06161H-3313), the same stack-up as the brain board.

Build: `python build_schematic.py`, `python build_pcb.py`, `python route_board.py`,
`python ../run_drc.py ClusterPanelTSD.kicad_pcb`, `python build_bom.py`,
`python ../review/layout_checks.py panel-tsd`, `python ../review/review_netlist.py panel-tsd`.

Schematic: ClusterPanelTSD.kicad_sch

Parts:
C1: 10u port 5V in; C_0805_2012Metric
C2: 100n port 5V in; C_0603_1608Metric
C3: 100n +1V8 (IOVCC) at the port; C_0603_1608Metric
C40: 4.7u boost in (AEC-Q200); C_0805_2012Metric
C41: 4.7u inverter in (AEC-Q200); C_0805_2012Metric
C42: 100n VIN filter (AEC-Q200); C_0603_1608Metric
C43: 220n VREF (AEC-Q200); C_0603_1608Metric
C44: 10n CP comp (AEC-Q200); C_0603_1608Metric
C45: 4n7 CN comp (AEC-Q200); C_0603_1608Metric
C46: 22u VPOS out 16V (AEC-Q200); C_1210_3225Metric
C47: 22u VNEG out 16V (AEC-Q200); C_1210_3225Metric
C48: 12p VPOS feed-forward (AEC-Q200); C_0603_1608Metric
C49: 15p VNEG feed-forward (AEC-Q200); C_0603_1608Metric
C50: 10u BL input (AEC-Q200); C_0805_2012Metric
C51: 220n BL COMP (AEC-Q200); C_0603_1608Metric
C52: 4.7u BL output, 50V part (AEC-Q200); C_1206_3216Metric
D2, D3, D4: PMEG6010ELRX (AEC-Q101, 60V/1A); Nexperia_CFP3_SOD-123W
J1: Screen port A input, Hirose FH12-40S-0.5SH; Hirose_FH12-40S-0.5SH_1x40-1MP_P0.50mm_Horizontal
J4: TST040HDBC-42 panel; Hirose_FH26-39S-0.3SHW_2Rows-39Pins-1MP_P0.60mm_Horizontal
JP1: SJ3 OPEN: bridge 1-2 if datasheet TABLE is right 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; SolderJumper-3_P1.3mm_Open_RoundedPad1.0x1.5mm
JP2: SJ3 OPEN: bridge 2-3 if datasheet TABLE is right 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; SolderJumper-3_P1.3mm_Open_RoundedPad1.0x1.5mm
L2: 4.7u boost (Coilcraft XAL4030-472ME); L_Coilcraft_XAL4030-XXX
L3: 4.7u inverter (Coilcraft XAL4030-472ME); L_Coilcraft_XAL4030-XXX
L4: 10u BL boost (Coilcraft XAL4040-103ME); L_Coilcraft_XAL4040-XXX
R1: 2.0k 1% panel ID (TSD TST040HDBC-42); R_0603_1608Metric
R37: 100R VIN filter; R_0603_1608Metric
R38: 511k VPOS top R1 (see docstring); R_0603_1608Metric
R39: 130k VPOS bottom R2 (see docstring); R_0603_1608Metric
R40: 499k VNEG top R3 (see docstring); R_0603_1608Metric
R41: 100k VNEG bottom R4 to VREF (see docstring); R_0603_1608Metric
R42: 1.10R LED current sense (0.2V/1.10=182mA); R_0603_1608Metric
R43: 100k bias-enable pulldown; R_0603_1608Metric
R50: 100k panel-reset pulldown; R_0603_1608Metric
U6: TPS65131-Q1; HVQFN-24-1EP_4x4mm_P0.5mm_EP2.5x2.5mm
U7: TPS61165-Q1; SOT-23-6

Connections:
+1V8: C3.1, J1.7 (+1V8), J4.13 (IOVCC), J4.14 (IOVCC)
+5V: C1.1, C2.1, C40.1, C41.1, C50.1, J1.2 (PORTA_5V), J1.3 (PORTA_5V), J1.4 (PORTA_5V), J1.5 (PORTA_5V), L2.1, L4.1, R37.1, U6.5 (INN1), U6.6 (INN2), U7.1 (VIN)
BL_COMP: C51.1, U7.5 (COMP)
BL_SW: D4.2, L4.2, U7.3 (SW)
DSI_CLK_N: J1.15 (DSI_CLK_N), J4.30 (CLK_N)
DSI_CLK_P: J1.16 (DSI_CLK_P), J4.28 (CLK_P)
DSI_D0_N: J1.21 (DSI_D0_N), J4.38 (LAN0_N)
DSI_D0_P: J1.22 (DSI_D0_P), J4.36 (LAN0_P)
DSI_D1_N: J1.18 (DSI_D1_N), J4.34 (LAN1_N)
DSI_D1_P: J1.19 (DSI_D1_P), J4.32 (LAN1_P)
DSI_D2_N: J1.12 (DSI_D2_N), J4.26 (LAN2_N)
DSI_D2_P: J1.13 (DSI_D2_P), J4.24 (LAN2_P)
DSI_PANEL_EN: J1.24 (PORTA_RESET), J4.16 (RESET), R50.1
GND: C1.2, C2.2, C3.2, C40.2, C41.2, C42.2, C43.2, C44.2, C45.2, C46.2, C47.2, C50.2, C51.2, C52.2, J1.1 (GND), J1.6 (GND), J1.8 (GND), J1.11 (GND), J1.14 (GND), J1.17 (GND), J1.20 (GND), J1.23 (GND), J1.28 (GND), J1.33 (GND), J1.38 (GND), J1.39 (GND), J1.40 (GND), J4.1 (GND), J4.6 (GND), J4.9 (GND), J4.12 (GND), J4.15 (GND), J4.17 (GND), J4.19 (GND), J4.23 (GND), J4.27 (GND), J4.31 (GND), J4.35 (GND), J4.39 (GND), L3.2, R1.2, R39.2, R42.2, R43.2, R50.2, U6.2 (PGND1), U6.3 (PGND2), U6.9 (PSP), U6.11 (PSN), U6.19 (AGND), U6.25 (EP), U7.4 (GND)
PANEL_BIAS_EN: J1.25 (PORTA_EN), R43.1, U6.8 (ENP), U6.10 (ENN)
PANEL_BIAS_VIN: C42.1, R37.2, U6.4 (VIN)
PANEL_BL_LEDA: C52.1, D4.1, J4.2 (LEDA), J4.3 (LEDA)
PANEL_BL_LEDK: J4.4 (LEDK), J4.5 (LEDK), R42.1, U7.6 (FB)
PANEL_BL_PWM: J1.26 (PORTA_BL_PWM), U7.2 (CTRL)
PANEL_BOOST_SW: D2.2, L2.2, U6.1 (INP1), U6.24 (INP2)
PANEL_CN: C45.1, U6.18 (CN)
PANEL_CP: C44.1, U6.21 (CP)
PANEL_FBN: C49.2, R40.2, R41.1, U6.16 (FBN)
PANEL_FBP: C48.2, R38.2, R39.1, U6.22 (FBP)
PANEL_ID: J1.32 (PORTA_ID), R1.1
PANEL_INV_SW: D3.1, L3.1, U6.13 (OUTN1), U6.14 (OUTN2)
PANEL_PIN_A: J4.7 (VPIN_A), J4.8 (VPIN_A), JP1.2 (COM)
PANEL_PIN_B: J4.10 (VPIN_B), J4.11 (VPIN_B), JP2.2 (COM)
PANEL_TE: J1.27 (PORTA_TE), J4.18 (TE)
PANEL_VREF: C43.1, R41.2, U6.17 (VREF)
PANEL_VSN: C47.1, C49.1, D3.2, JP1.3 (B), JP2.3 (B), R40.1, U6.15 (VNEG)
PANEL_VSP: C46.1, C48.1, D2.1, JP1.1 (A), JP2.1 (A), R38.1, U6.23 (VPOS)
